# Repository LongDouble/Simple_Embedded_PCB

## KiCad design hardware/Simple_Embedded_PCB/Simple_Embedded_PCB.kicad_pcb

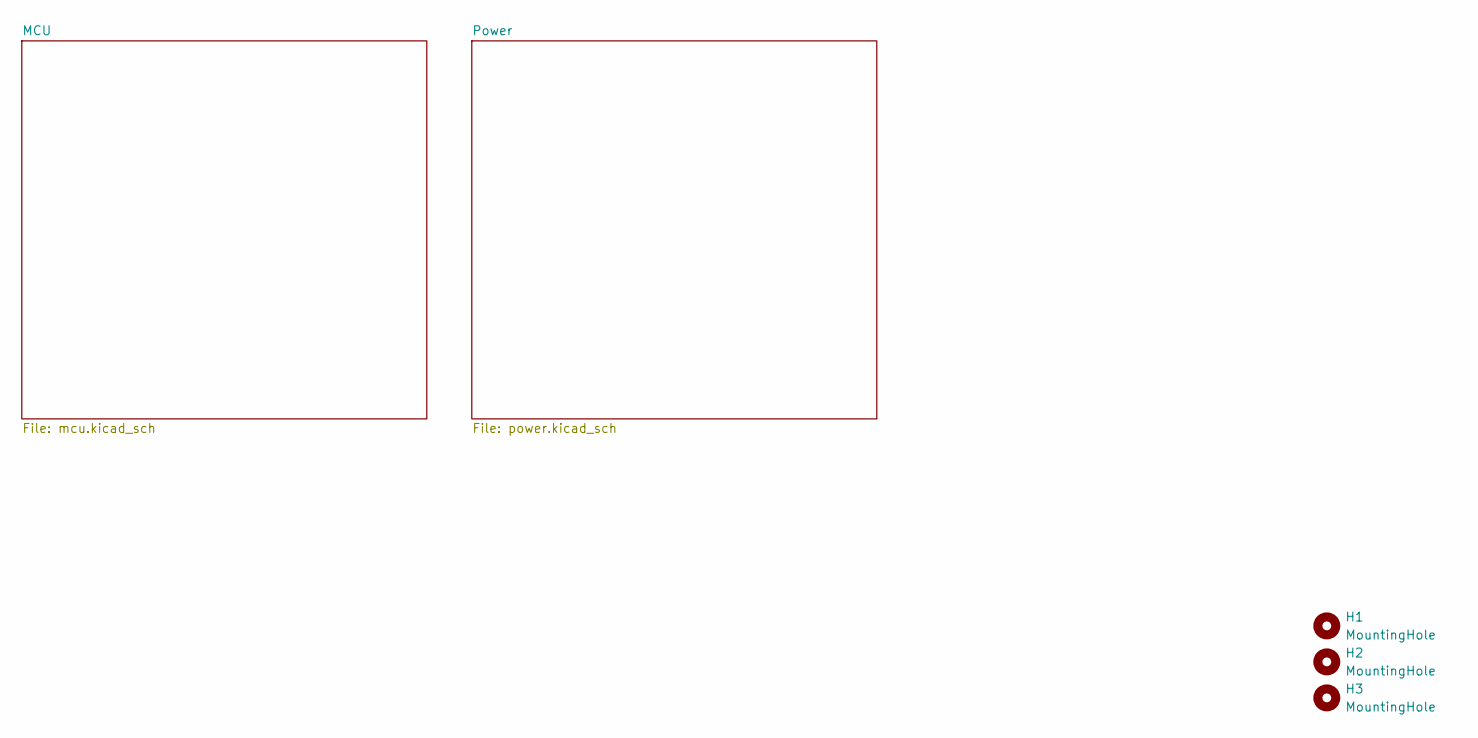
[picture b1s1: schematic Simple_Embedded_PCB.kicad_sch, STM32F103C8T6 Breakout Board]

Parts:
H1, H2, H3: MountingHole; ToolingHole_JLCPCB

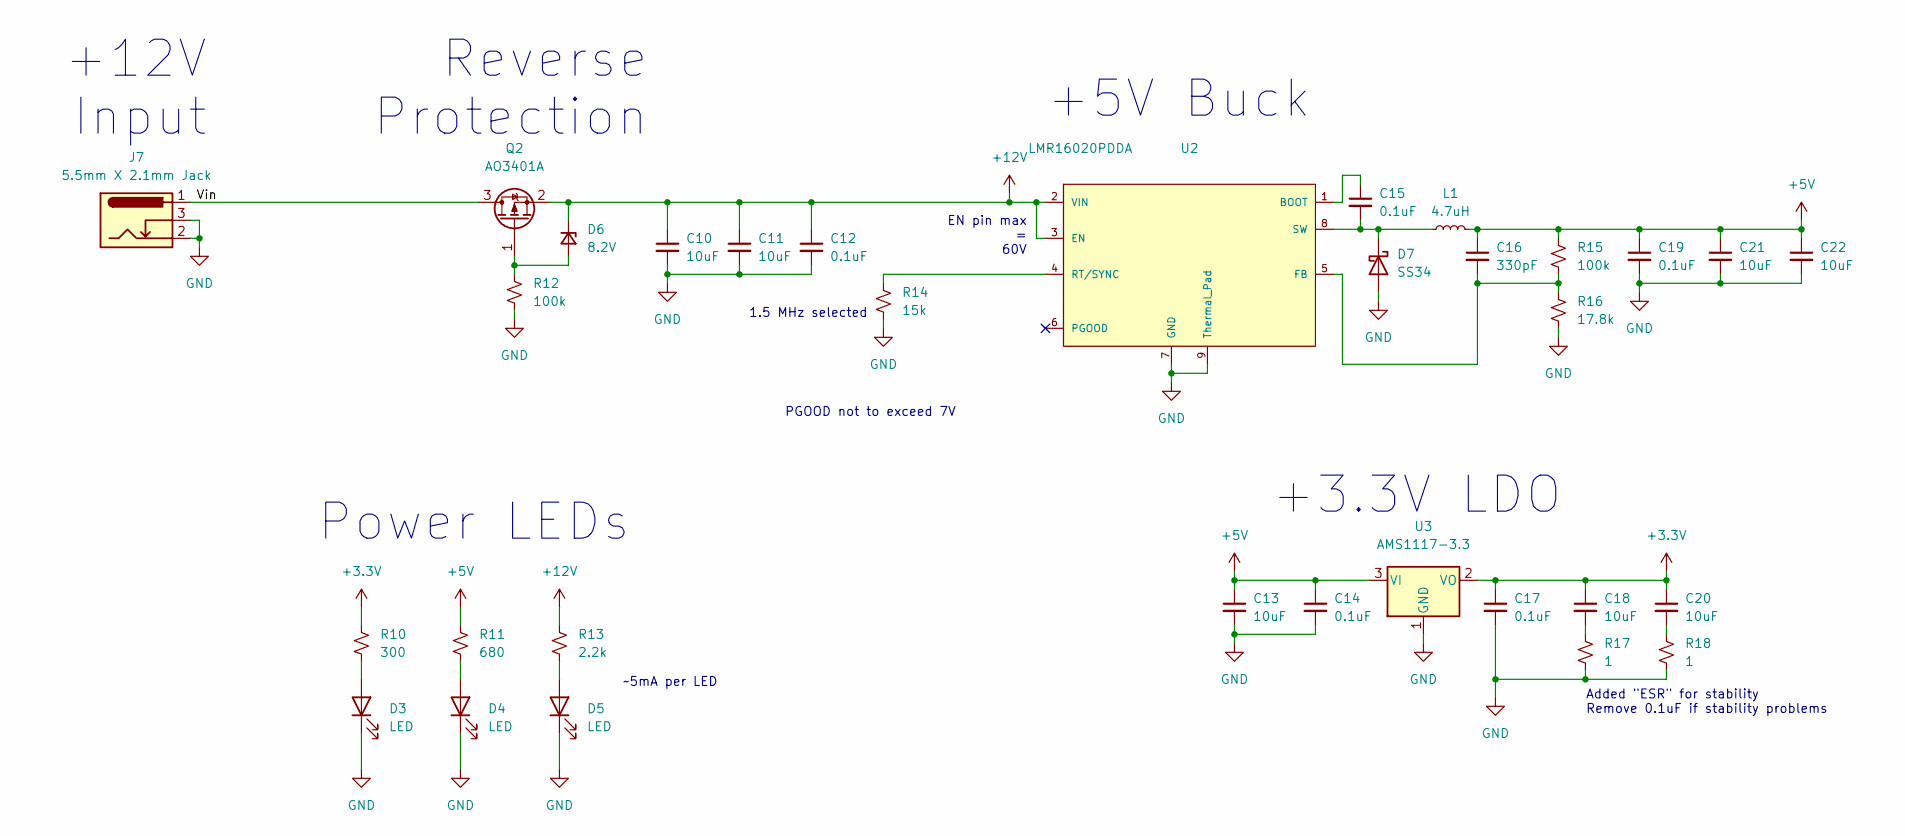
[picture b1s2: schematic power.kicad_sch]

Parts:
C10, C11, C18, C20, C21, C22: 10uF; C_1206_3216Metric; LCSC Part Number C13585
C12: 0.1uF; C_0603_1608Metric; LCSC Part Number C14663
C13: 10uF; C_0805_2012Metric; LCSC Part Number C440198
C14, C17, C19: 0.1uF; C_0402_1005Metric; LCSC Part Number C307331
C15: 0.1uF; C_0402_1005Metric; Voltage 50V; LCSC Part Number C307331
C16: 330pF; C_0402_1005Metric; LCSC Part Number C13533
D3, D4, D5: LED; LED_0805_2012Metric; LCSC Part Number C2297
D6: 8.2V; D_SOD-123; LCSC Part Number C235988
D7: SS34; D_SMA; LCSC Part Number C8678
J7: 5.5mm X 2.1mm Jack; BarrelJack_Horizontal
L1: 4.7uH; SUNLORD_SWPA6045S4R7MT; LCSC Part Number C78804
Q2: AO3401A; SOT-23; LCSC Part Number C15127
R10: 300; R_0603_1608Metric; LCSC Part Number C23025
R11: 680; R_0603_1608Metric; LCSC Part Number C23228
R12: 100k; R_0603_1608Metric; LCSC Part Number C25803
R13: 2.2k; R_0603_1608Metric; LCSC Part Number C4190
R14: 15k; R_0402_1005Metric; LCSC Part Number C25756
R15: 100k; R_0402_1005Metric; LCSC Part Number C25741
R16: 17.8k; R_0402_1005Metric; LCSC Part Number C226819
R17, R18: 1; R_0603_1608Metric; LCSC Part Number C22936
U2: LMR16020PDDA; 8-PowerSOIC; output voltage 0.8-50V; mouser part number 595-LMR16020PDDA; digikey description IC REG BUCK ADJUSTABLE 2A 8SOPWR
U3: AMS1117-3.3; SOT-223-3_TabPin2; LCSC Part Number C6186

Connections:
+3.3V: C17.1, C18.1, C20.1, R10.2, U3.2 (VO); also elsewhere on the board
+5V: C13.1, C14.1, C16.1, C19.1, C21.1, C22.1, L1.2, R11.2, R15.2, U3.3 (VI); also elsewhere on the board
+12V: C10.1, C11.1, C12.1, D6.1 (K), Q2.2 (S), R13.2, U2.2 (VIN), U2.3 (EN)
/Power/Vin: J7.1, Q2.3 (D)
GND: C10.2, C11.2, C12.2, C13.2, C14.2, C17.2, C19.2, C21.2, C22.2, D3.1 (K), D4.1 (K), D5.1 (K), D7.2 (A), J7.2, J7.3, R12.2, R14.1, R16.1, R17.1, R18.1, U2.7 (GND), U2.9 (Thermal_Pad), U3.1 (GND); also elsewhere on the board
unnamed: C15.1, U2.1 (BOOT)
unnamed: C15.2, D7.1 (K), L1.1, U2.8 (SW)
unnamed: C16.2, R15.1, R16.2, U2.5 (FB)
unnamed: C18.2, R17.2
unnamed: C20.2, R18.2
unnamed: D3.2 (A), R10.1
unnamed: D4.2 (A), R11.1
unnamed: D5.2 (A), R13.1
unnamed: D6.2 (A), Q2.1 (G), R12.1
unnamed: R14.2, U2.4 (RT/SYNC)

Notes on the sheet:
Power LEDs
Reverse Protection
1.5 MHz selected
EN pin max = 60V
Added "ESR" for stability Remove 0.1uF if stability problems
~5mA per LED
PGOOD not to exceed 7V
+5V Buck
+12V Input
+3.3V LDO

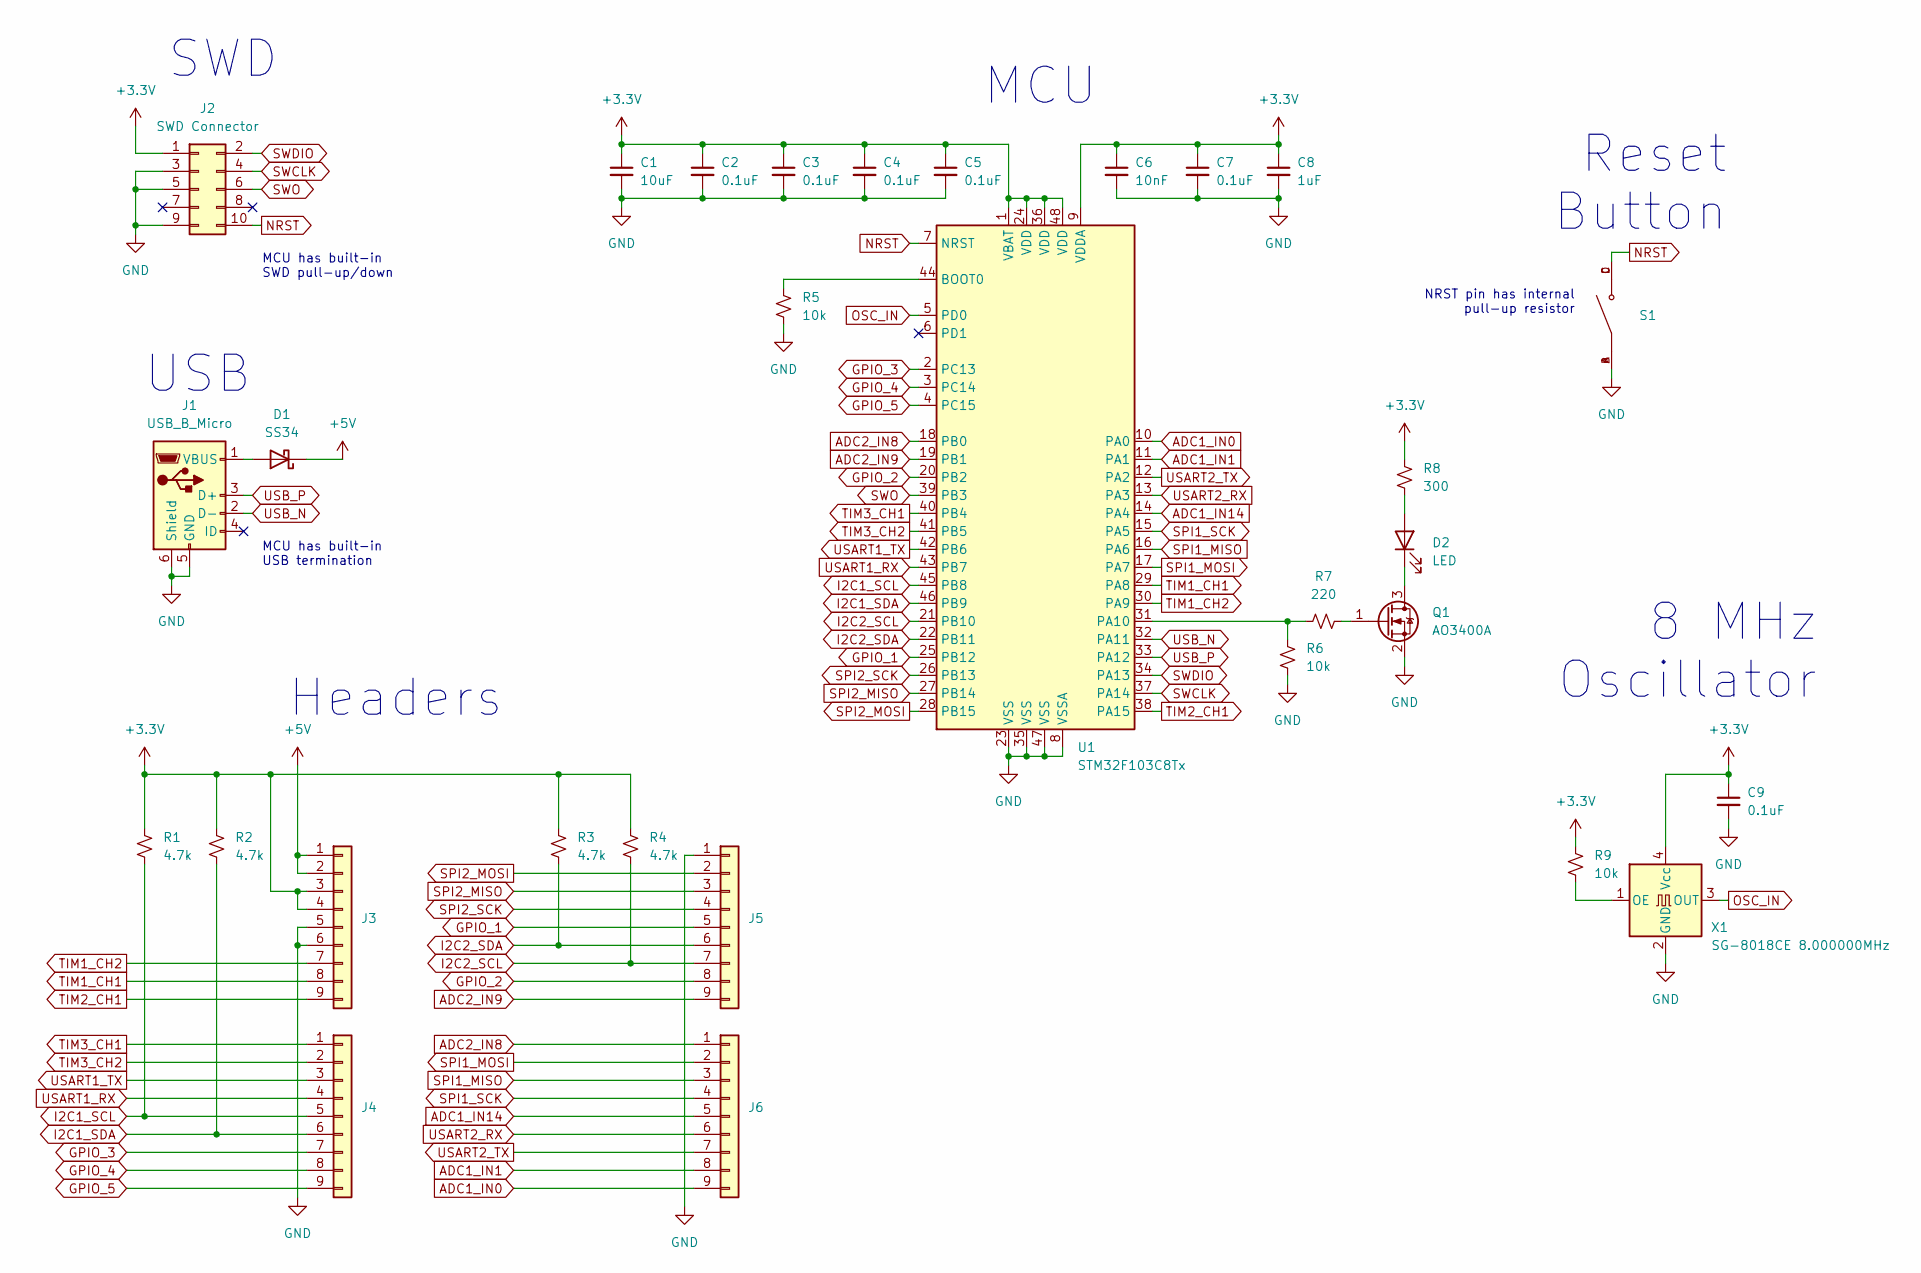
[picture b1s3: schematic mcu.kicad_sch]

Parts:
C1: 10uF; C_0805_2012Metric; LCSC Part Number C440198
C2, C3, C4, C5, C7, C9: 0.1uF; C_0402_1005Metric; LCSC Part Number C307331
C6: 10nF; C_0402_1005Metric; LCSC Part Number C15195
C8: 1uF; C_0603_1608Metric; LCSC Part Number C15849
D1: SS34; D_SMA; LCSC Part Number C8678
D2: LED; LED_0805_2012Metric; LCSC Part Number C2297
J1: USB_B_Micro; USB_Micro-B_Amphenol_10118194_Horizontal; LCSC Part Number C132563
J2: SWD Connector; Amphenol-20021121-0-0-0; LCSC Part Number C598540
J3, J4, J5, J6: Conn_01x09; PinHeader_1x09_P2.54mm_Vertical
Q1: AO3400A; SOT-23; LCSC Part Number C20917
R1, R2, R3, R4: 4.7k; R_0402_1005Metric; LCSC Part Number C25900
R5, R6, R9: 10k; R_0402_1005Metric; LCSC Part Number C25744
R7: 220; R_0402_1005Metric; LCSC Part Number C25091
R8: 300; R_0603_1608Metric; LCSC Part Number C23025
S1: TS-1187A-B-A-B; SW_TS-1187A-B-A-B
U1: STM32F103C8Tx; LQFP-48_7x7mm_P0.5mm; LCSC Part Number C8734
X1: SG-8018CE 8.000000MHz; Oscillator_SMD_SeikoEpson_SG8002CE-4Pin_3.2x2.5mm; LCSC Part Number C390495

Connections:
+3.3V: C1.1, C2.1, C3.1, C4.1, C5.1, C6.1, C7.1, C8.1, C9.1, J2.1, J3.3, J3.4, R1.1, R2.1, R3.1, R4.1, R8.2, R9.1, U1.1 (VBAT), U1.9 (VDDA), U1.24 (VDD), U1.36 (VDD), U1.48 (VDD), X1.4 (Vcc); also elsewhere on the board
+5V: D1.1 (K), J3.1, J3.2; also elsewhere on the board
ADC1_IN0: J6.9, U1.10 (PA0)
ADC1_IN1: J6.8, U1.11 (PA1)
ADC1_IN14: J6.5, U1.14 (PA4)
ADC2_IN8: J6.1, U1.18 (PB0)
ADC2_IN9: J5.9, U1.19 (PB1)
GND: C1.2, C2.2, C3.2, C4.2, C5.2, C6.2, C7.2, C8.2, C9.2, J1.5 (GND), J1.6 (Shield), J2.3, J2.5, J2.9, J3.5, J3.6, J5.1, Q1.2 (S), R5.2, R6.2, S1.A, S1.B, U1.8 (VSSA), U1.23 (VSS), U1.35 (VSS), U1.47 (VSS), X1.2 (GND); also elsewhere on the board
GPIO_1: J5.5, U1.25 (PB12)
GPIO_2: J5.8, U1.20 (PB2)
GPIO_3: J4.7, U1.2 (PC13)
GPIO_4: J4.8, U1.3 (PC14)
GPIO_5: J4.9, U1.4 (PC15)
I2C1_SCL: J4.5, R1.2, U1.45 (PB8)
I2C1_SDA: J4.6, R2.2, U1.46 (PB9)
I2C2_SCL: J5.7, R4.2, U1.21 (PB10)
I2C2_SDA: J5.6, R3.2, U1.22 (PB11)
NRST: J2.10, S1.C, S1.D, U1.7 (NRST)
unnamed: D1.2 (A), J1.1 (VBUS)
unnamed: D2.1 (K), Q1.3 (D)
unnamed: D2.2 (A), R8.1
unnamed: Q1.1 (G), R7.2
unnamed: R5.1, U1.44 (BOOT0)
unnamed: R6.1, R7.1, U1.31 (PA10)
unnamed: R9.2, X1.1 (OE)
OSC_IN: U1.5 (PD0), X1.3 (OUT)
SPI1_MISO: J6.3, U1.16 (PA6)
SPI1_MOSI: J6.2, U1.17 (PA7)
SPI1_SCK: J6.4, U1.15 (PA5)
SPI2_MISO: J5.3, U1.27 (PB14)
SPI2_MOSI: J5.2, U1.28 (PB15)
SPI2_SCK: J5.4, U1.26 (PB13)
SWCLK: J2.4, U1.37 (PA14)
SWDIO: J2.2, U1.34 (PA13)
SWO: J2.6, U1.39 (PB3)
TIM1_CH1: J3.8, U1.29 (PA8)
TIM1_CH2: J3.7, U1.30 (PA9)
TIM2_CH1: J3.9, U1.38 (PA15)
TIM3_CH1: J4.1, U1.40 (PB4)
TIM3_CH2: J4.2, U1.41 (PB5)
USART1_RX: J4.4, U1.43 (PB7)
USART1_TX: J4.3, U1.42 (PB6)
USART2_RX: J6.6, U1.13 (PA3)
USART2_TX: J6.7, U1.12 (PA2)
USB_N: J1.2 (D-), U1.32 (PA11)
USB_P: J1.3 (D+), U1.33 (PA12)

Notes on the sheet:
USB
MCU
Headers
8 MHz Oscillator
MCU has built-in USB termination
SWD
MCU has built-in SWD pull-up/down
Reset Button
NRST pin has internal pull-up resistor

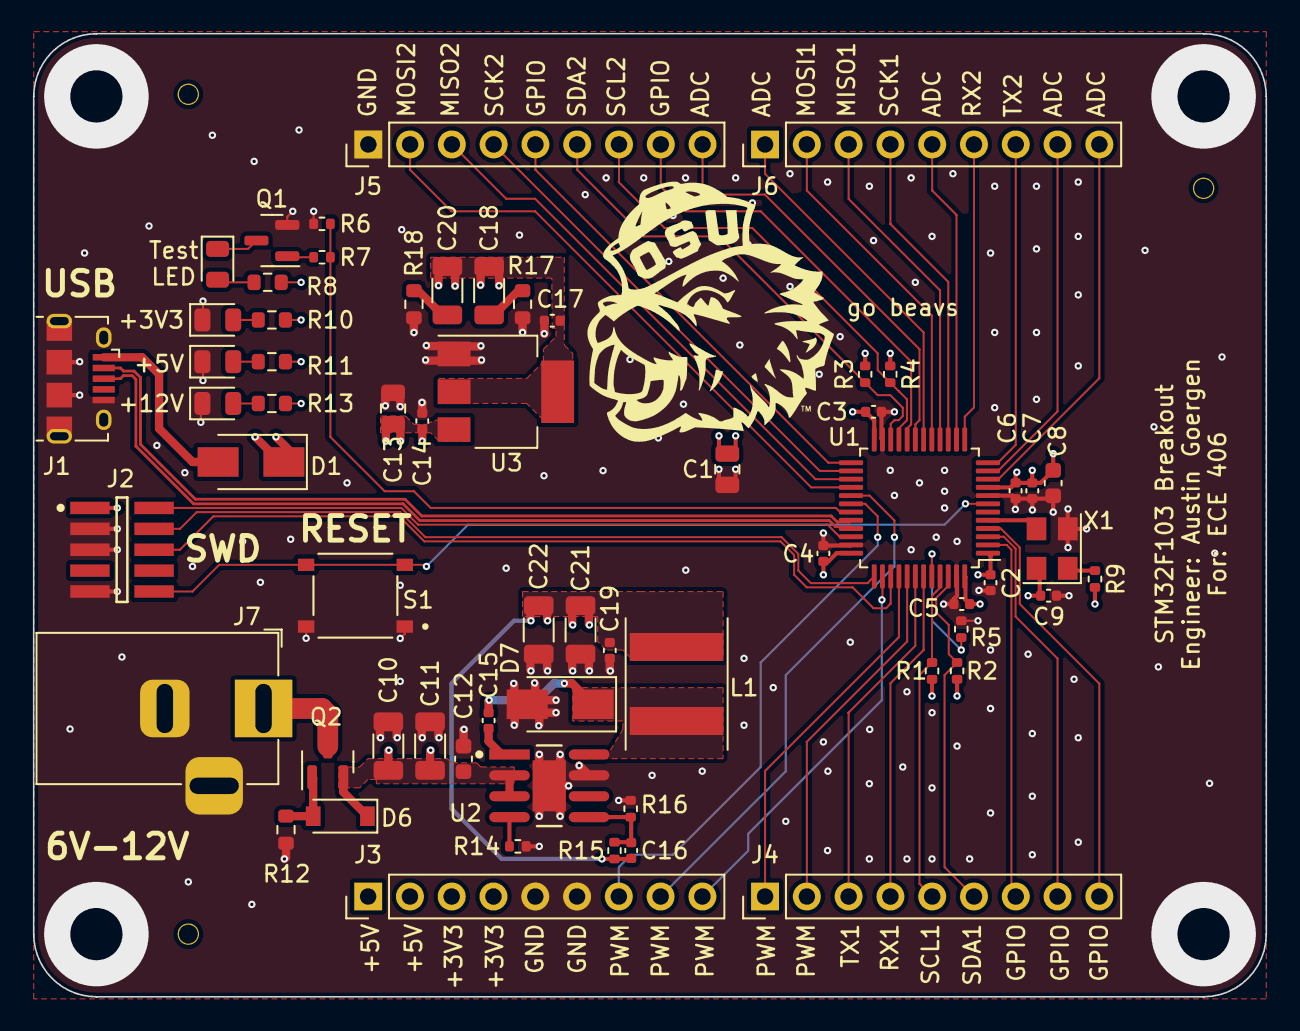
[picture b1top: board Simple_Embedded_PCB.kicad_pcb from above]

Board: 4 copper layers, 74.9 x 58.5 mm, 65 parts (0 on the bottom side), 58 nets.

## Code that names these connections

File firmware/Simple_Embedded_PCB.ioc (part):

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Mcu.Name=STM32F103C(8-B)Tx
Mcu.Package=LQFP48
Mcu.UserName=STM32F103C8Tx
PA0-WKUP.Signal=ADCx_IN0
PA1.Signal=ADCx_IN1
PA10.GPIOParameters=GPIO_Label
PA10.GPIO_Label=PWM_LED
PA10.Signal=S_TIM1_CH3
PA11.Mode=Device
PA11.Signal=USB_DM
PA12.Mode=Device
PA12.Signal=USB_DP
PA13.Mode=Trace_Asynchronous_SW
PA13.Signal=SYS_JTMS-SWDIO
PA14.Mode=Trace_Asynchronous_SW
PA14.Signal=SYS_JTCK-SWCLK
PA15.Signal=S_TIM2_CH1_ETR
PA2.Mode=Asynchronous
PA2.Signal=USART2_TX
PA3.Mode=Asynchronous
PA3.Signal=USART2_RX
PA4.Signal=ADCx_IN4
PA5.Mode=Full_Duplex_Master
PA5.Signal=SPI1_SCK
PA6.Mode=Full_Duplex_Master
PA6.Signal=SPI1_MISO
PA7.Mode=Full_Duplex_Master
PA7.Signal=SPI1_MOSI
PA8.Signal=S_TIM1_CH1
PA9.Signal=S_TIM1_CH2
PB0.Signal=ADCx_IN8
PB1.Signal=ADCx_IN9
PB10.Mode=I2C
PB10.Signal=I2C2_SCL
PB11.Mode=I2C
PB11.Signal=I2C2_SDA
PB12.Signal=GPIO_Output
PB13.Mode=Full_Duplex_Master
PB13.Signal=SPI2_SCK
PB14.Mode=Full_Duplex_Master
PB14.Signal=SPI2_MISO
PB15.Mode=Full_Duplex_Master
PB15.Signal=SPI2_MOSI
PB2.Signal=GPIO_Output
PB3.Mode=Trace_Asynchronous_SW
PB3.Signal=SYS_JTDO-TRACESWO
PB4.Signal=S_TIM3_CH1
PB5.Signal=S_TIM3_CH2
PB6.Mode=Asynchronous
PB6.Signal=USART1_TX
PB7.Mode=Asynchronous
PB7.Signal=USART1_RX
PB8.Mode=I2C
PB8.Signal=I2C1_SCL
PB9.Mode=I2C
PB9.Signal=I2C1_SDA
PC13-TAMPER-RTC.Signal=GPIO_Output
PC14-OSC32_IN.Signal=GPIO_Output
PC15-OSC32_OUT.Signal=GPIO_Output
PD0-OSC_IN.Mode=HSE-External-Clock-Source
PD0-OSC_IN.Signal=RCC_OSC_IN
PD1-OSC_OUT.Mode=HSE-External-Clock-Source
PD1-OSC_OUT.Signal=RCC_OSC_OUT
RCC.SYSCLKFreq_VALUE=72000000
RCC.SYSCLKSource=RCC_SYSCLKSOURCE_PLLCLK
board=custom

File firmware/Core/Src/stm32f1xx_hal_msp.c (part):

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
    __HAL_RCC_GPIOA_CLK_ENABLE();
    /**ADC1 GPIO Configuration
    PA0-WKUP     ------> ADC1_IN0
    PA1     ------> ADC1_IN1
    PA4     ------> ADC1_IN4
    */
    GPIO_InitStruct.Pin = GPIO_PIN_0|GPIO_PIN_1|GPIO_PIN_4;
    GPIO_InitStruct.Mode = GPIO_MODE_ANALOG;
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
    __HAL_RCC_GPIOB_CLK_ENABLE();
    /**ADC2 GPIO Configuration
    PB0     ------> ADC2_IN8
    PB1     ------> ADC2_IN9
    */
    GPIO_InitStruct.Pin = GPIO_PIN_0|GPIO_PIN_1;
    GPIO_InitStruct.Mode = GPIO_MODE_ANALOG;
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    __HAL_RCC_ADC1_CLK_DISABLE();

    /**ADC1 GPIO Configuration
    PA0-WKUP     ------> ADC1_IN0
    PA1     ------> ADC1_IN1
    PA4     ------> ADC1_IN4
    */
    HAL_GPIO_DeInit(GPIOA, GPIO_PIN_0|GPIO_PIN_1|GPIO_PIN_4);

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    __HAL_RCC_ADC2_CLK_DISABLE();

    /**ADC2 GPIO Configuration
    PB0     ------> ADC2_IN8
    PB1     ------> ADC2_IN9
    */
    HAL_GPIO_DeInit(GPIOB, GPIO_PIN_0|GPIO_PIN_1);

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
    __HAL_RCC_GPIOB_CLK_ENABLE();
    /**I2C1 GPIO Configuration
    PB8     ------> I2C1_SCL
    PB9     ------> I2C1_SDA
    */
    GPIO_InitStruct.Pin = GPIO_PIN_8|GPIO_PIN_9;
    GPIO_InitStruct.Mode = GPIO_MODE_AF_OD;
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
    __HAL_RCC_GPIOB_CLK_ENABLE();
    /**I2C2 GPIO Configuration
    PB10     ------> I2C2_SCL
    PB11     ------> I2C2_SDA
    */
    GPIO_InitStruct.Pin = GPIO_PIN_10|GPIO_PIN_11;
    GPIO_InitStruct.Mode = GPIO_MODE_AF_OD;
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    __HAL_RCC_I2C1_CLK_DISABLE();

    /**I2C1 GPIO Configuration
    PB8     ------> I2C1_SCL
    PB9     ------> I2C1_SDA
    */
    HAL_GPIO_DeInit(GPIOB, GPIO_PIN_8);

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    __HAL_RCC_I2C2_CLK_DISABLE();

    /**I2C2 GPIO Configuration
    PB10     ------> I2C2_SCL
    PB11     ------> I2C2_SDA
    */
    HAL_GPIO_DeInit(GPIOB, GPIO_PIN_10);

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
    __HAL_RCC_GPIOA_CLK_ENABLE();
    /**SPI1 GPIO Configuration
    PA5     ------> SPI1_SCK
    PA6     ------> SPI1_MISO
    PA7     ------> SPI1_MOSI
    */
    GPIO_InitStruct.Pin = GPIO_PIN_5|GPIO_PIN_7;
    GPIO_InitStruct.Mode = GPIO_MODE_AF_PP;
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
    __HAL_RCC_GPIOB_CLK_ENABLE();
    /**SPI2 GPIO Configuration
    PB13     ------> SPI2_SCK
    PB14     ------> SPI2_MISO
    PB15     ------> SPI2_MOSI
    */
    GPIO_InitStruct.Pin = GPIO_PIN_13|GPIO_PIN_15;
    GPIO_InitStruct.Mode = GPIO_MODE_AF_PP;
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    __HAL_RCC_SPI1_CLK_DISABLE();

    /**SPI1 GPIO Configuration
    PA5     ------> SPI1_SCK
    PA6     ------> SPI1_MISO
    PA7     ------> SPI1_MOSI
    */
    HAL_GPIO_DeInit(GPIOA, GPIO_PIN_5|GPIO_PIN_6|GPIO_PIN_7);

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    __HAL_RCC_SPI2_CLK_DISABLE();

    /**SPI2 GPIO Configuration
    PB13     ------> SPI2_SCK
    PB14     ------> SPI2_MISO
    PB15     ------> SPI2_MOSI
    */
    HAL_GPIO_DeInit(GPIOB, GPIO_PIN_13|GPIO_PIN_14|GPIO_PIN_15);

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  /* USER CODE END TIM1_MspPostInit 0 */
    __HAL_RCC_GPIOA_CLK_ENABLE();
    /**TIM1 GPIO Configuration
    PA8     ------> TIM1_CH1
    PA9     ------> TIM1_CH2
    PA10     ------> TIM1_CH3
    */
    GPIO_InitStruct.Pin = GPIO_PIN_8|GPIO_PIN_9|PWM_LED_Pin;
    GPIO_InitStruct.Mode = GPIO_MODE_AF_PP;
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
    __HAL_RCC_GPIOA_CLK_ENABLE();
    /**TIM2 GPIO Configuration
    PA15     ------> TIM2_CH1
    */
    GPIO_InitStruct.Pin = GPIO_PIN_15;
    GPIO_InitStruct.Mode = GPIO_MODE_AF_PP;
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
    __HAL_RCC_GPIOB_CLK_ENABLE();
    /**TIM3 GPIO Configuration
    PB4     ------> TIM3_CH1
    PB5     ------> TIM3_CH2
    */
    GPIO_InitStruct.Pin = GPIO_PIN_4|GPIO_PIN_5;
    GPIO_InitStruct.Mode = GPIO_MODE_AF_PP;
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
    __HAL_RCC_GPIOB_CLK_ENABLE();
    /**USART1 GPIO Configuration
    PB6     ------> USART1_TX
    PB7     ------> USART1_RX
    */
    GPIO_InitStruct.Pin = GPIO_PIN_6;
    GPIO_InitStruct.Mode = GPIO_MODE_AF_PP;
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
    __HAL_RCC_GPIOA_CLK_ENABLE();
    /**USART2 GPIO Configuration
    PA2     ------> USART2_TX
    PA3     ------> USART2_RX
    */
    GPIO_InitStruct.Pin = GPIO_PIN_2;
    GPIO_InitStruct.Mode = GPIO_MODE_AF_PP;
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    __HAL_RCC_USART1_CLK_DISABLE();

    /**USART1 GPIO Configuration
    PB6     ------> USART1_TX
    PB7     ------> USART1_RX
    */
    HAL_GPIO_DeInit(GPIOB, GPIO_PIN_6|GPIO_PIN_7);

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    __HAL_RCC_USART2_CLK_DISABLE();

    /**USART2 GPIO Configuration
    PA2     ------> USART2_TX
    PA3     ------> USART2_RX
    */
    HAL_GPIO_DeInit(GPIOA, GPIO_PIN_2|GPIO_PIN_3);

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
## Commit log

2022-10-09 Created firmware with pin configurations
2022-10-17 Started schematic. Added MCU, decoupling caps, reset switch, oscillator, USB connector, SWD connector, 3.3 volt and 5 volt power leds, PWM led, input power and reset protection
2022-10-18 Update Simple_Embedded_PCB.kicad_sch
    Added 5V and 3.3V regulators, add unpopulated header pins
2022-10-20 Split MCU and Power into different sheets, created header pinouts, finished schematic and annotation
2022-10-21 Added 4.7k pullups to I2C and reannotated
2022-10-21 Removed comment regarding PGOOD floating, changed PGOOD PU resistor
2022-10-22 Preliminary layout done, removed resistors from PGOOD to just leave it floating
2022-10-22 Setup design rules and created proper board outline with mounting holes
2022-10-22 Routed all PCB traces, began routing power
2022-10-23 Finished layout, added step models and silkscreen
2022-10-23 Added tooling holes and put JLCPCB order number on back of board, added kicad_prl file to git ignore
2022-10-23 Removed kicad_prl file
2022-10-23 Added JLCPCB part numbers
2022-10-23 Board ordered! Created Gerber files, drill files, BOM, and parts placement file.
2022-10-23 Removing extra copy of BOM
2022-11-20 Changed KiCad project to use symbols, footprints, and 3D models from project itself.
2022-11-20 Updating .gitignore, removing file that don't need to be in repo
2022-12-04 Removed dead library and duplicate files
2022-12-08 Changed size of oscillator 3D model to a realistic size

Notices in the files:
firmware/Core/Src/stm32f1xx_hal_msp.c:
Copyright (c) 2022 STMicroelectronics.
All rights reserved.
This software is licensed under terms that can be found in the LICENSE file
